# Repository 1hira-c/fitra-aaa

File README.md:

# fitra-aaa

Raytac **AN54LV-15**（Nordic **nRF54L15** 搭載 BLE モジュール）を中心とした、
**SlimeVR フルボディトラッカー基板**（[Smol Slime](https://docs.slimevr.dev/smol-slimes/index.html) 向け）の
KiCad 設計プロジェクトです。

## 概要

| 機能 | 部品 |
|------|------|
| MCU / BLE SoC | Raytac **AN54LV-15**（Nordic **nRF54L15** 搭載モジュール） |
| 6軸 IMU センサ | STMicroelectronics **LSM6DSV** |
| 電源管理（PMIC） | Nordic Semiconductor **NPM2100** (QFN) |
| 低周波クロック | Micro Crystal **CM8V-T1A 32.768 kHz** |
| バッテリ接続 | **VBAT / GND 独立スルーホール端子** |
| 書き込み / デバッグ | 基板上の **SWD パッド** |

## Smol Slime / SlimeVR について

本基板は、nRF 系 SoC 向けの SlimeVR トラッカー firmware「**Smol Slime**」で動作する
トラッカーハードウェアです。

- Smol Slime ドキュメント: <https://docs.slimevr.dev/smol-slimes/index.html>
- トラッカー firmware（SlimeNRF）: <https://github.com/SlimeVR/SlimeVR-Tracker-nRF>
- SlimeVR プロジェクト: <https://docs.slimevr.dev/>

## 必要環境

- **KiCad 9 以降**（回路図は KiCad 10 で保存されています。**KiCad 10 を推奨**）

## 開き方

`fitra-aaa.kicad_pro` を KiCad で開いてください。

## 外部ライブラリについて

回路図・基板で使用しているシンボル/フットプリントは設計ファイル（`*.kicad_sch` の
`lib_symbols` および `*.kicad_pcb`）に**埋め込まれている**ため、リポジトリをクローン
すればそのまま**閲覧・製造データ（ガーバー等）の生成が可能**です。外部ライブラリを
再ダウンロードしなくても基板は完全に表示されます。

部品のシンボル/フットプリントを**再編集**する場合のみ、元ライブラリが必要です。

### 同梱しているライブラリ

| ライブラリ | 内容 | ライセンス |
|-----------|------|-----------|
| `libraries/local_lib*` | 自作シンボル/フットプリント（SWD パッド, VBAT スルー, nPM2100-QFN 等） | 本プロジェクトに準ずる（CC-BY-4.0） |

### 同梱していないライブラリ（設計に埋め込み済み／再編集時に各サイトから取得）

下記の部品ライブラリは**単体ファイルとしてはリポジトリに含めていません**。各提供元の
ライセンス・利用規約により、ライブラリ単体での再配布が制限されているためです。
シンボル/フットプリントは設計ファイルに埋め込み済みなので閲覧・製造には支障ありません。

| 部品 | 取得元 | 備考 |
|------|--------|------|
| NPM2100（PMIC） | [SnapEDA](https://www.snapeda.com/) | CC-BY-SA 4.0。単体ライブラリの再配布は制限あり。設計の一部としての利用は許諾 |
| LSM6DSV16XTR（IMU） | [SnapEDA](https://www.snapeda.com/) | 同上 |
| CM8V-T1A-32.768KHZ（クリスタル） | [SnapEDA](https://www.snapeda.com/) | 同上 |
| AN54LV（BLE モジュール） | [Raytac](https://www.raytac.com/) | Altium 形式。提供元規約により同梱不可 |

> 再編集が必要な場合は各提供元から入手し、`libraries/` 配下に配置のうえ
> `fp-lib-table` / `sym-lib-table` に再登録してください。

## クレジット / 帰属表示

- **NPM2100** / **LSM6DSV16XTR** / **CM8V-T1A-32.768KHZ** のシンボル・フットプリント・3D モデルは
  [SnapEDA](https://www.snapeda.com/)（CC-BY-SA 4.0）提供のものを設計に組み込んで使用しています。

## ライセンス

本リポジトリの設計データ（回路図・基板・自作ライブラリ）は
**Creative Commons Attribution 4.0 International (CC-BY-4.0)** で公開します。

同梱・参照する各部品ライブラリは、それぞれの提供元（SnapEDA, Raytac 等）
のライセンス・利用規約に従います。

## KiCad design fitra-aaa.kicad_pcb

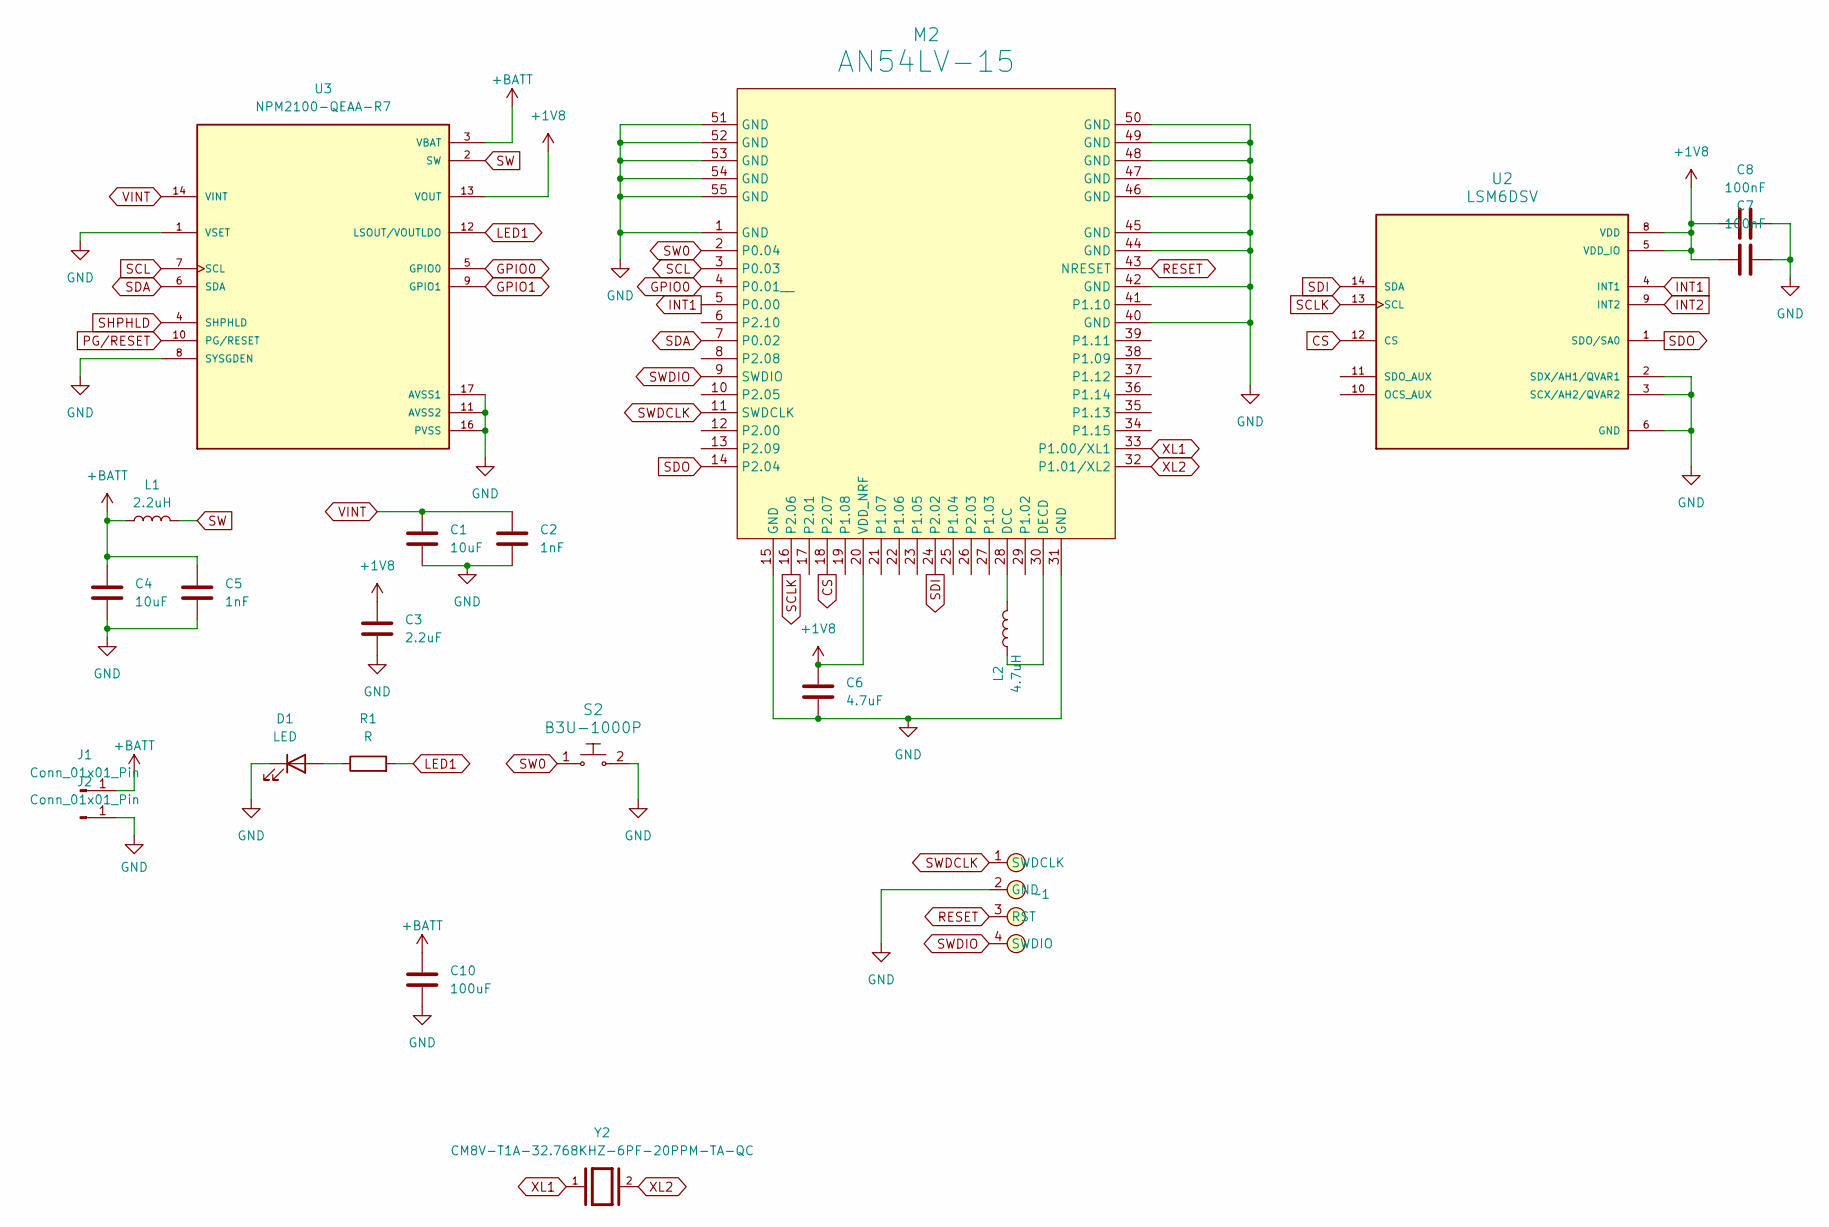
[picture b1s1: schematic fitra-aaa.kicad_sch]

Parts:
C1, C4: 10uF; C_0402_1005Metric
C2, C5: 1nF; C_0201_0603Metric
C3: 2.2uF; C_0402_1005Metric
C6: 4.7uF; C_0402_1005Metric
C7, C8: 100nF; C_0402_1005Metric
C10: 100uF; C_0805_2012Metric
D1: LED; LED_2-SMD_No_Lead_1.7x0.8mm
J1, J2: Conn_01x01_Pin; Pin_D0.7mm_L6.5mm_W1.8mm_FlatFork
L1: 2.2uH; L_0603_1608Metric
L2: 4.7uH; L_0603_1608Metric
M2: AN54LV-15
R1: R; R_0603_1608Metric
S2: B3U-1000P; Switch_Tactile_SMD_B3U-1000P; MPN B3U-1000P; Digi-Key_PN SW1020CT-ND
U2: LSM6DSV; XDCR_LSM6DSV16XTR; PARTREV 4
U3: NPM2100-QEAA-R7; QFN65P400X400X90-17N; PARTREV 1.0
Y2: CM8V-T1A-32.768KHZ-6PF-20PPM-TA-QC; XTAL_CM8V-T1A-32.768KHZ-6PF-20PPM-TA-QC; PARTREV 8.1/11.2018; DigiKey_Part_Number 2195-CM8V-T1A-32.768KHZ-6PF-20PPM-TA-QC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
~1: SWD_Pad

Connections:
+1V8: C3.1, C6.1, C7.1, C8.1, M2.20 (VDD_NRF), U2.5 (VDD_IO), U2.8 (VDD), U3.13 (VOUT)
+BATT: C4.1, C5.1, C10.1, J1.1 (Pin_1_1), L1.1, U3.3 (VBAT)
CS: M2.18 (P2.07), U2.12 (CS)
GND: C1.2, C2.2, C3.2, C4.2, C5.2, C6.2, C7.2, C8.2, C10.2, D1.1 (K), J2.1 (Pin_1_1), M2.1 (GND), M2.15 (GND), M2.31 (GND), M2.40 (GND), M2.42 (GND), M2.44 (GND), M2.45 (GND), M2.46 (GND), M2.47 (GND), M2.48 (GND), M2.49 (GND), M2.50 (GND), M2.51 (GND), M2.52 (GND), M2.53 (GND), M2.54 (GND), M2.55 (GND), S2.2, U2.2 (SDX/AH1/QVAR1), U2.3 (SCX/AH2/QVAR2), U2.6 (GND), U2.7 (GND), U3.1 (VSET), U3.8 (SYSGDEN), U3.11 (AVSS2), U3.16 (PVSS), U3.17 (AVSS1), ~1.2 (GND)
GPIO0: M2.4 (P0.01__), U3.5 (GPIO0)
GPIO1: U3.9 (GPIO1)
INT1: M2.5 (P0.00), U2.4 (INT1)
INT2: U2.9 (INT2)
LED1: R1.2, U3.12 (LSOUT/VOUTLDO)
unnamed: D1.2 (A), R1.1
unnamed: L2.2, M2.28 (DCC)
unnamed: L2.1, M2.30 (DECD)
PG/RESET: U3.10 (PG/RESET)
RESET: M2.43 (NRESET), ~1.3 (RST)
SCL: M2.3 (P0.03), U3.7 (SCL)
SCLK: M2.16 (P2.06), U2.13 (SCL)
SDA: M2.7 (P0.02), U3.6 (SDA)
SDI: M2.24 (P2.02), U2.14 (SDA)
SDO: M2.14 (P2.04), U2.1 (SDO/SA0)
SHPHLD: U3.4 (SHPHLD)
SW: L1.2, U3.2 (SW)
SW0: M2.2 (P0.04), S2.1
SWDCLK: M2.11 (SWDCLK), ~1.1 (SWDCLK)
SWDIO: M2.9 (SWDIO), ~1.4 (SWDIO)
VINT: C1.1, C2.1, U3.14 (VINT), U3.15 (VINT)
XL1: M2.33 (P1.00/XL1), Y2.1
XL2: M2.32 (P1.01/XL2), Y2.2

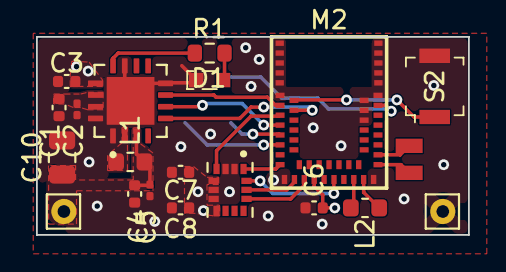
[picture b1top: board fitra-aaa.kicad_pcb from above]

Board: 4 copper layers, 24.0 x 11.0 mm, 20 parts (0 on the bottom side), 20 nets.
